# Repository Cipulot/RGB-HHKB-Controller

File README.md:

# RGB HHKB Controller

 HHKB Pro 2 Keyboard Controller Board with RGB strip support.

## Introduction

This project is a continuation of my development of open source EC boards.

It's a derivative of the [Hasu HHKB Controller](https://github.com/tmk/HHKB_controller) with an updated MCU package and RGB strip support.

This board is USB-mode only and is **NOT** compatible with the BLE options.

## Technical information

- Microcontroller: Atmel Atmega32U4
- Connector:
  - USB-C
  - HHKB ANSI connector
  - HHKB JP connector
- Firmware compatibility: QMK (with VIA/VIAL support)
- Protection hardware (on all connection methods):
  - Fused
  - ESD protection
-RGB strip connector, both THT and SMD pad on both sides of the board.

## Renders and Prototypes

### Render

### Prototype

TBD

## Revisions and relative features

### Rev1

This revision implements all the main features of the PCB.

The controller is electrically compatible with both the ANSI and JP version of the HHKB keyboard but you will need to chose between the 2 connectors.

#### Connector choice

Pay attention at the time or ordering the PCBs to populate only one of the 2 connectors:

- `S13B-ZR-SM4A-TF` for ANSI
- `DF14A-15P-1.25H` for JP

## License

<br />This work is licensed under a <a rel="license" href="http://creativecommons.org/licenses/by-nc-sa/4.0/">Creative Commons Attribution-NonCommercial-ShareAlike 4.0 International License</a>.

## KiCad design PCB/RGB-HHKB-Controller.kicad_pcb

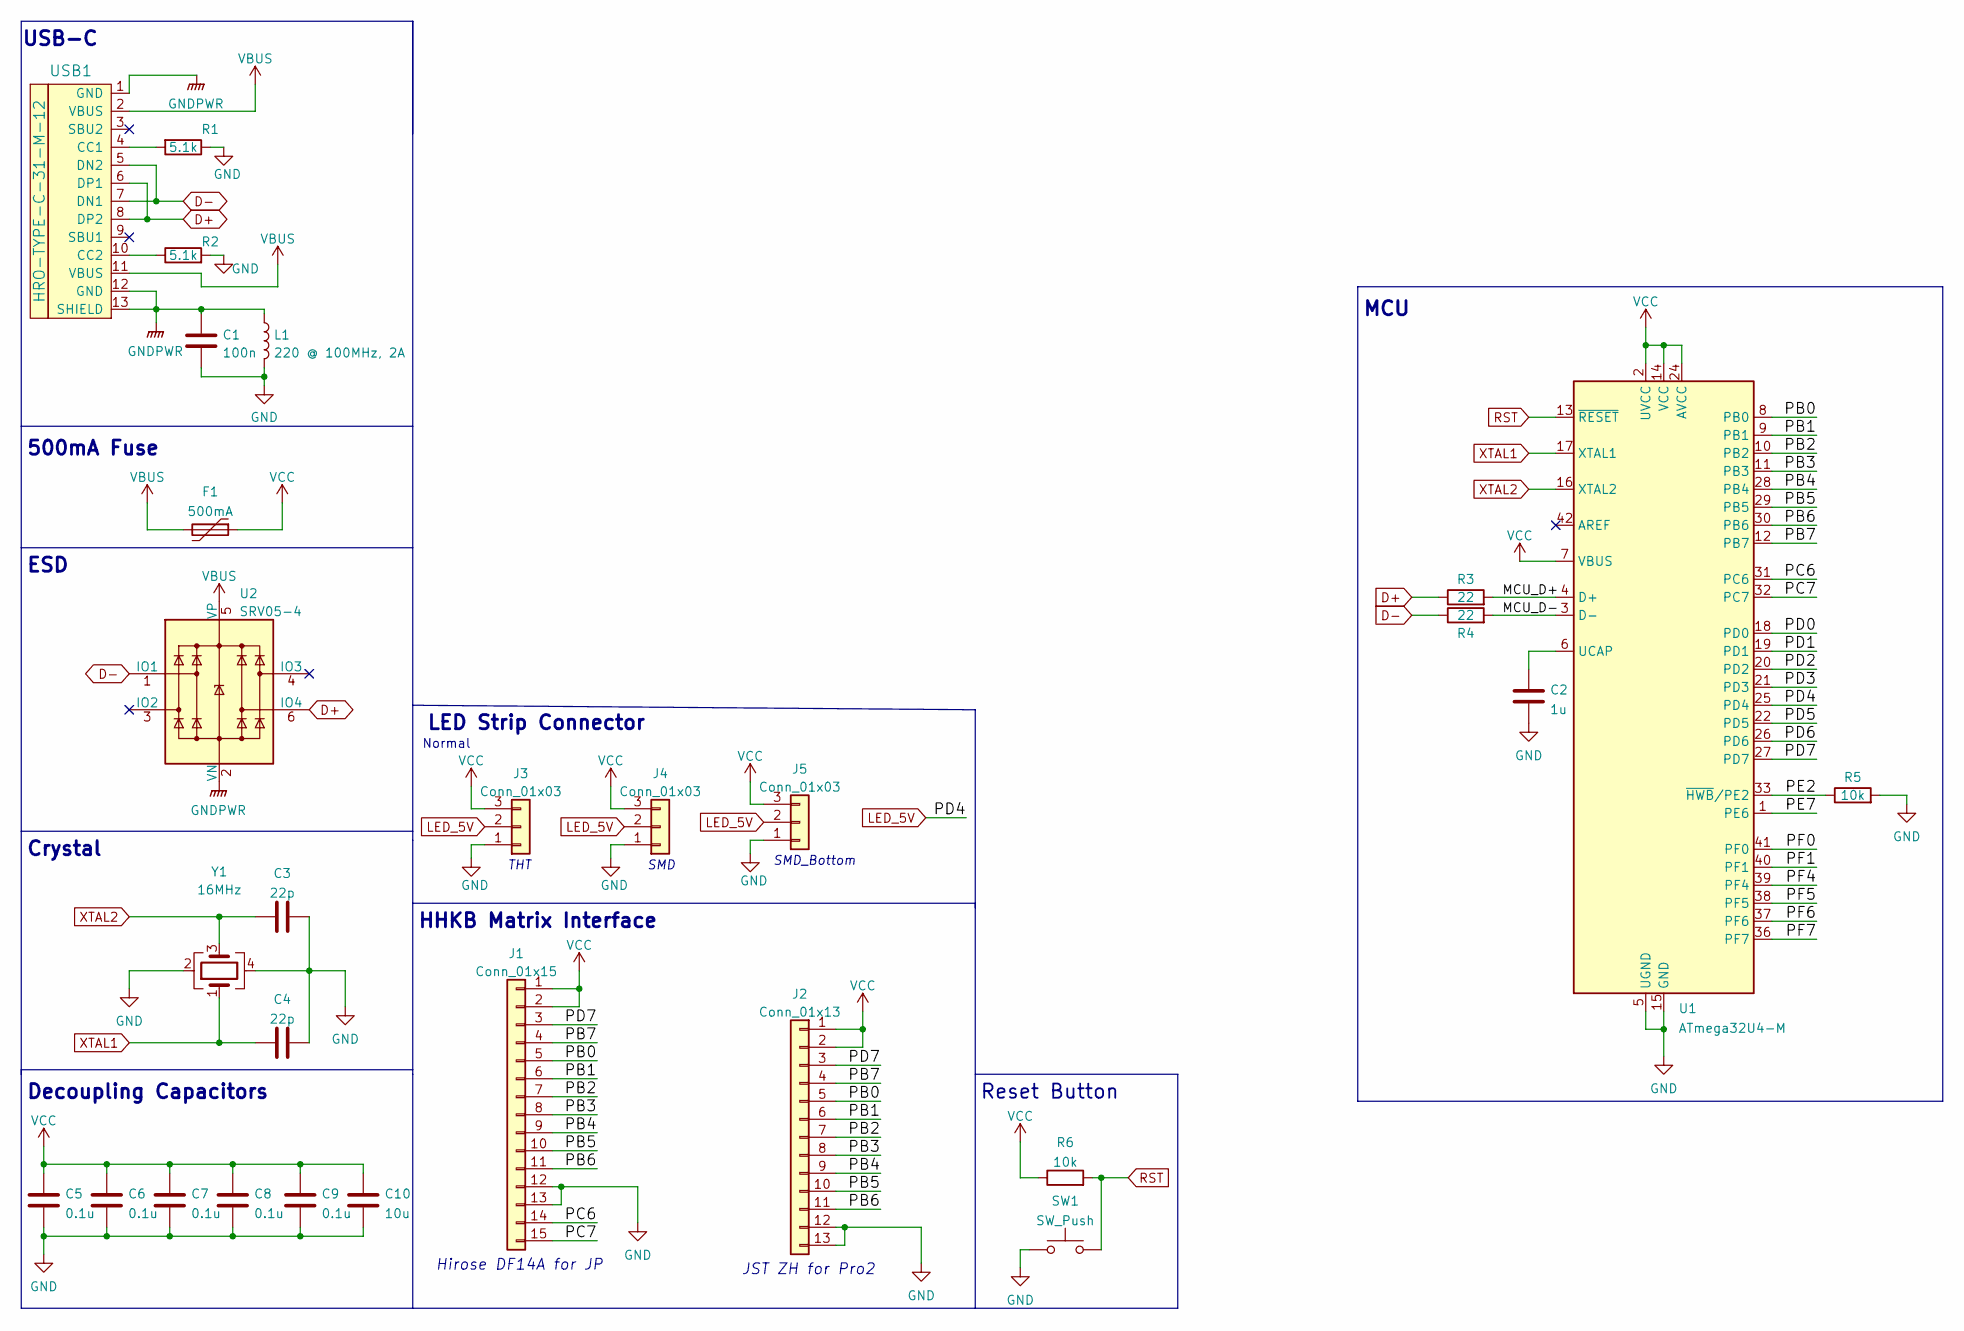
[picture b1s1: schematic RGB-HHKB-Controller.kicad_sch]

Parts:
C1: 100n; C_0603_1608Metric; LCSC C14663
C2: 1u; C_0603_1608Metric; LCSC C15849
C3, C4: 22p; C_0603_1608Metric; LCSC C1653
C5, C6, C7, C8, C9: 0.1u; C_0603_1608Metric; LCSC C14663
C10: 10u; C_0603_1608Metric; LCSC C96446
F1: 500mA; Fuse_1206_3216Metric; LCSC C70076
J1: Conn_01x15; DF14A-15P-1.25H
J2: Conn_01x13; S13B-ZR-SM4A-TF
J3: Conn_01x03; PinHeader_1x03_P2.00mm_Vertical
J4, J5: Conn_01x03; LED_Strip_Pad
L1: 220 @ 100MHz, 2A; L_0603_1608Metric; LCSC C85832
R1, R2: 5.1k; R_0402_1005Metric; LCSC C25905
R3, R4: 22; R_0603_1608Metric; LCSC C23345
R5: 10k; R_0603_1608Metric
R6: 10k; R_0603_1608Metric; LCSC C25804
SW1: SW_Push; SW_Tactile_SKHH_Angled; LCSC C139763
U1: ATmega32U4-M; QFN-44-1EP_7x7mm_P0.5mm_EP5.2x5.2mm; LCSC C112161
U2: SRV05-4; SOT-23-6-routable; LCSC C85364
USB1: HRO-TYPE-C-31-M-12; HRO-TYPE-C-31-M-12-Assembly; LCSC C165948
Y1: 16MHz; Crystal_SMD_3225-4pin_3.2x2.5mm; LCSC C13738

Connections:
/MCU_D+: R3.2, U1.4 (D+)
/MCU_D-: R4.2, U1.3 (D-)
/PB0: J1.5, J2.5, U1.8 (PB0)
/PB1: J1.6, J2.6, U1.9 (PB1)
/PB2: J1.7, J2.7, U1.10 (PB2)
/PB3: J1.8, J2.8, U1.11 (PB3)
/PB4: J1.9, J2.9, U1.28 (PB4)
/PB5: J1.10, J2.10, U1.29 (PB5)
/PB6: J1.11, J2.11, U1.30 (PB6)
/PB7: J1.4, J2.4, U1.12 (PB7)
/PC6: J1.14, U1.31 (PC6)
/PC7: J1.15, U1.32 (PC7)
/PD0: U1.18 (PD0)
/PD1: U1.19 (PD1)
/PD2: U1.20 (PD2)
/PD3: U1.21 (PD3)
/PD5: U1.22 (PD5)
/PD6: U1.26 (PD6)
/PD7: J1.3, J2.3, U1.27 (PD7)
/PE2: R5.1, U1.33 (~HWB/PE2)
/PE7: U1.1 (PE6)
/PF0: U1.41 (PF0)
/PF1: U1.40 (PF1)
/PF4: U1.39 (PF4)
/PF5: U1.38 (PF5)
/PF6: U1.37 (PF6)
/PF7: U1.36 (PF7)
D+: R3.1, U2.6 (IO4), USB1.6 (DP1), USB1.8 (DP2)
D-: R4.1, U2.1 (IO1), USB1.5 (DN2), USB1.7 (DN1)
GND: C1.2, C2.2, C3.1, C4.1, C5.2, C6.2, C7.2, C8.2, C9.2, C10.2, J1.12, J1.13, J2.12, J2.13, J3.1, J4.1, J5.1, L1.2, R1.1, R2.2, R5.2, SW1.1, U1.5 (UGND), U1.15 (GND), U1.23 (GND), U1.35 (GND), U1.43 (GND), U1.45 (GND), Y1.2, Y1.4
GNDPWR: C1.1, L1.1, U2.2 (VN), USB1.1 (GND), USB1.12 (GND), USB1.13 (SHIELD)
LED_5V: J3.2, J4.2, J5.2, U1.25 (PD4)
unnamed: C2.1, U1.6 (UCAP)
unnamed: R1.2, USB1.4 (CC1)
unnamed: R2.1, USB1.10 (CC2)
RST: R6.2, SW1.2, U1.13 (~RESET)
VBUS: F1.2, U2.5 (VP), USB1.2 (VBUS), USB1.11 (VBUS)
VCC: C5.1, C6.1, C7.1, C8.1, C9.1, C10.1, F1.1, J1.1, J1.2, J2.1, J2.2, J3.3, J4.3, J5.3, R6.1, U1.2 (UVCC), U1.7 (VBUS), U1.14 (VCC), U1.24 (AVCC), U1.34 (VCC), U1.44 (AVCC)
XTAL1: C4.2, U1.17 (XTAL1), Y1.1
XTAL2: C3.2, U1.16 (XTAL2), Y1.3

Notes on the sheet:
LED Strip Connector
SMD_Bottom
JST ZH for Pro2
Crystal
SMD
500mA Fuse
Hirose DF14A for JP
Decoupling Capacitors
MCU
USB-C
Reset Button
ESD
THT
HHKB Matrix Interface
Normal

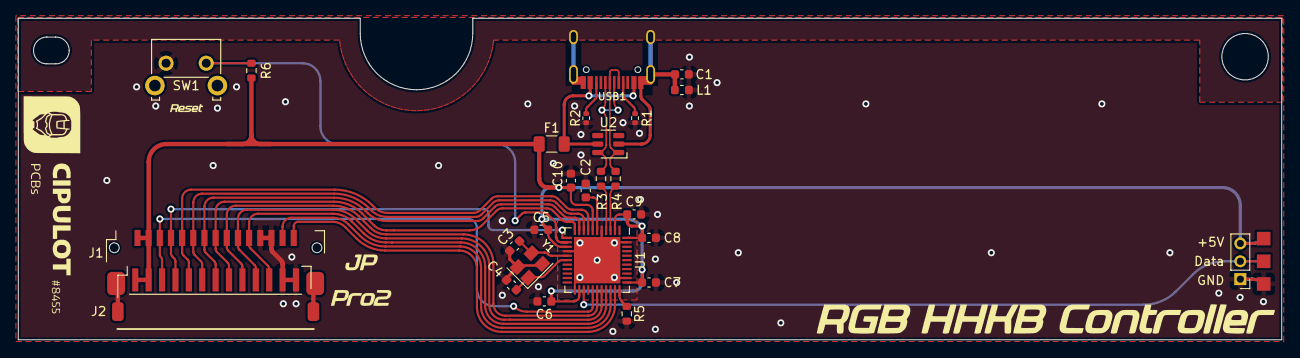
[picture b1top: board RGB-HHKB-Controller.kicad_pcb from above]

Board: 2 copper layers, 141.5 x 36.0 mm, 28 parts (0 on the bottom side), 27 nets.

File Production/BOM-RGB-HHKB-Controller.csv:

Comment,Designator,Footprint,LCSC,MPN
ATmega32U4-M,U1,QFN-44-1EP_7x7mm_P0.5mm_EP5.2x5.2mm,C112161,
16MHz,Y1,Crystal_SMD_3225-4pin_3.2x2.5mm,C13738,
100n,"C1,C5,C6,C7,C8,C9",C_0603_1608Metric,C14663,
1u,C2,C_0603_1608Metric,C15849,
22p,"C3,C4",C_0603_1608Metric,C1653,
HRO-TYPE-C-31-M-12,USB1,HRO-TYPE-C-31-M-12-Assembly,C165948,
22,"R3,R4",R_0603_1608Metric,C23345,
10k,"R5,R6",R_0603_1608Metric,C25804,
5.1k,"R1,R2",R_0402_1005Metric,C25905,
SW_Push,SW1,SW_Tactile_SKHH_Angled,C318884,
500mA,F1,Fuse_1206_3216Metric,C70076,
SRV05-4,U2,SOT-23-6-routable,C85364,
"220 @ 100MHz, 2A",L1,L_0603_1608Metric,C85832,
10u,C10,C_0603_1608Metric,C96446,
Conn_01x15,J1,DF14A-15P-1.25H,DF14A-15P-1.25H,DF14A-15P-1.25H
Conn_01x13,J2,S13B-ZR-SM4A-TF,S13B-ZR-SM4A-TF(LF)(SN),S13B-ZR-SM4A-TF(LF)(SN)

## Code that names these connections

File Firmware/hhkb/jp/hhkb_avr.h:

/*
Copyright 2022 Cipulot

This program is free software: you can redistribute it and/or modify
it under the terms of the GNU General Public License as published by
the Free Software Foundation, either version 2 of the License, or
(at your option) any later version.

This program is distributed in the hope that it will be useful,
but WITHOUT ANY WARRANTY; without even the implied warranty of
MERCHANTABILITY or FITNESS FOR A PARTICULAR PURPOSE.  See the
GNU General Public License for more details.

You should have received a copy of the GNU General Public License
along with this program.  If not, see <http://www.gnu.org/licenses/>.
*/

#pragma once

#include <stdint.h>
#include <stdbool.h>
#include <avr/io.h>
#include <avr/interrupt.h>
#include <util/delay.h>

// Timer resolution check
#if (1000000 / TIMER_RAW_FREQ > 20)
#    error "Timer resolution(>20us) is not enough for HHKB matrix scan tweak on V-USB."
#endif

/*
 * HHKB Matrix I/O
 *
 * row:     HC4051[A,B,C]  selects scan row0-7
 * row-ext: [En0,En1] row extention for JP
 * col:     LS145[A,B,C,D] selects scan col0-7 and enable(D)
 * key:     on: 0/off: 1
 * prev:    hysteresis control: assert(1) when previous key state is on
 */

#if defined(__AVR_ATmega32U4__)
/*
 * For TMK HHKB alt controller(ATMega32U4)
 *
 * row:     PB0-2
 * col:     PB3-5,6
 * key:     PD7(pull-uped)
 * prev:    PB7
 * power:   PD4(L:off/H:on)
 * row-ext: PC6,7 for HHKB JP(active low)
 */
static inline void KEY_ENABLE(void) {
    (PORTB &= ~(1 << 6));
}
static inline void KEY_UNABLE(void) {
    (PORTB |= (1 << 6));
}
static inline bool KEY_STATE(void) {
    return (PIND & (1 << 7));
}
static inline void KEY_PREV_ON(void) {
    (PORTB |= (1 << 7));
}
static inline void KEY_PREV_OFF(void) {
    (PORTB &= ~(1 << 7));
}
#    ifdef HHKB_POWER_SAVING
static inline void KEY_POWER_ON(void) {
    DDRB  = 0xFF;
    PORTB = 0x40; // change pins output
    DDRD |= (1 << 4);
    PORTD |= (1 << 4); // MOS FET switch on
    /* Without this wait you will miss or get false key events. */
    _delay_ms(5); // wait for powering up
}
static inline void KEY_POWER_OFF(void) {
    /* input with pull-up consumes less than without it when pin is open. */
    DDRB  = 0x00;
    PORTB = 0xFF; // change pins input with pull-up
    DDRD |= (1 << 4);
    PORTD &= ~(1 << 4); // MOS FET switch off
}
static inline bool KEY_POWER_STATE(void) {
    return PORTD & (1 << 4);
}
#    else
static inline void KEY_POWER_ON(void) {}
static inline void KEY_POWER_OFF(void) {}
static inline bool KEY_POWER_STATE(void) {
    return true;
}
#    endif
static inline void KEY_INIT(void) {
    /* row,col,prev: output */
    DDRB  = 0xFF;
    PORTB = 0x40; // unable
    /* key: input with pull-up */
    DDRD &= ~0x80;
    PORTD |= 0x80;

    /* row extention for HHKB JP */
    DDRC |= (1 << 6 | 1 << 7);
    PORTC |= (1 << 6 | 1 << 7);

    KEY_UNABLE();
    KEY_PREV_OFF();

    KEY_POWER_OFF();
}
static inline void KEY_SELECT(uint8_t ROW, uint8_t COL) {
    PORTB = (PORTB & 0xC0) | (((COL)&0x07) << 3) | ((ROW)&0x07);

    if ((ROW)&0x08)
        PORTC = (PORTC & ~(1 << 6 | 1 << 7)) | (1 << 6);
    else
        PORTC = (PORTC & ~(1 << 6 | 1 << 7)) | (1 << 7);
}

#elif defined(__AVR_AT90USB1286__)
/*
 * For Teensy++(AT90USB1286)
 *
 *                          HHKB pro    HHKB pro2
 * row:     PB0-2           (6-8)       (5-7)
 * col:     PB3-5,6         (9-12)      (8-11)
 * key:     PE6(pull-uped)  (4)         (3)
 * prev:    PE7             (5)         (4)
 *
 * TODO: convert into 'staitc inline' function
 */
#    define KEY_INIT()         \
        do {                   \
            DDRB |= 0x7F;      \
            DDRE |= (1 << 7);  \
            DDRE &= ~(1 << 6); \
            PORTE |= (1 << 6); \
        } while (0)
#    define KEY_SELECT(ROW, COL) (PORTB = (PORTB & 0xC0) | (((COL)&0x07) << 3) | ((ROW)&0x07))
#    define KEY_ENABLE() (PORTB &= ~(1 << 6))
#    define KEY_UNABLE() (PORTB |= (1 << 6))
#    define KEY_STATE() (PINE & (1 << 6))
#    define KEY_PREV_ON() (PORTE |= (1 << 7))
#    define KEY_PREV_OFF() (PORTE &= ~(1 << 7))
#    define KEY_POWER_ON()
#    define KEY_POWER_OFF()
#    define KEY_POWER_STATE() true

#else
#    error "define code for matrix scan"
#endif

#if 0
// For ATMega328P with V-USB
//
// #elif defined(__AVR_ATmega328P__)
// Ports for V-USB
// key:     PB0(pull-uped)
// prev:    PB1
// row:     PB2-4
// col:     PC0-2,3
// power:   PB5(Low:on/Hi-z:off)
#    define KEY_INIT()         \
        do {                   \
            DDRB |= 0x3E;      \
            DDRB &= ~(1 << 0); \
            PORTB |= 1 << 0;   \
            DDRC |= 0x0F;      \
            KEY_UNABLE();      \
            KEY_PREV_OFF();    \
        } while (0)
#    define KEY_SELECT(ROW, COL)                        \
        do {                                            \
            PORTB = (PORTB & 0xE3) | ((ROW)&0x07) << 2; \
            PORTC = (PORTC & 0xF8) | ((COL)&0x07);      \
        } while (0)
#    define KEY_ENABLE() (PORTC &= ~(1 << 3))
#    define KEY_UNABLE() (PORTC |= (1 << 3))
#    define KEY_STATE() (PINB & (1 << 0))
#    define KEY_PREV_ON() (PORTB |= (1 << 1))
#    define KEY_PREV_OFF() (PORTB &= ~(1 << 1))
// Power supply switching
#    define KEY_POWER_ON()      \
        do {                    \
            KEY_INIT();         \
            PORTB &= ~(1 << 5); \
            _delay_ms(1);       \
        } while (0)
#    define KEY_POWER_OFF() \
        do {                \
            DDRB &= ~0x3F;  \
            PORTB &= ~0x3F; \
            DDRC &= ~0x0F;  \
            PORTC &= ~0x0F; \
        } while (0)
#endif

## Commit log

2022-08-16 Asset Init
2022-08-16 Firmware Init
2022-08-16 PCB project init
2022-08-16 Production files init
2022-08-16 Firmware Code dump
2023-11-15 Update LICENSE
    Change of License
2024-03-03 Updated the License for the project and relative details.

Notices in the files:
PCB/RGB-HHKB-Controller.kicad_pcb:
CC-BY-NC-SA-4.0
